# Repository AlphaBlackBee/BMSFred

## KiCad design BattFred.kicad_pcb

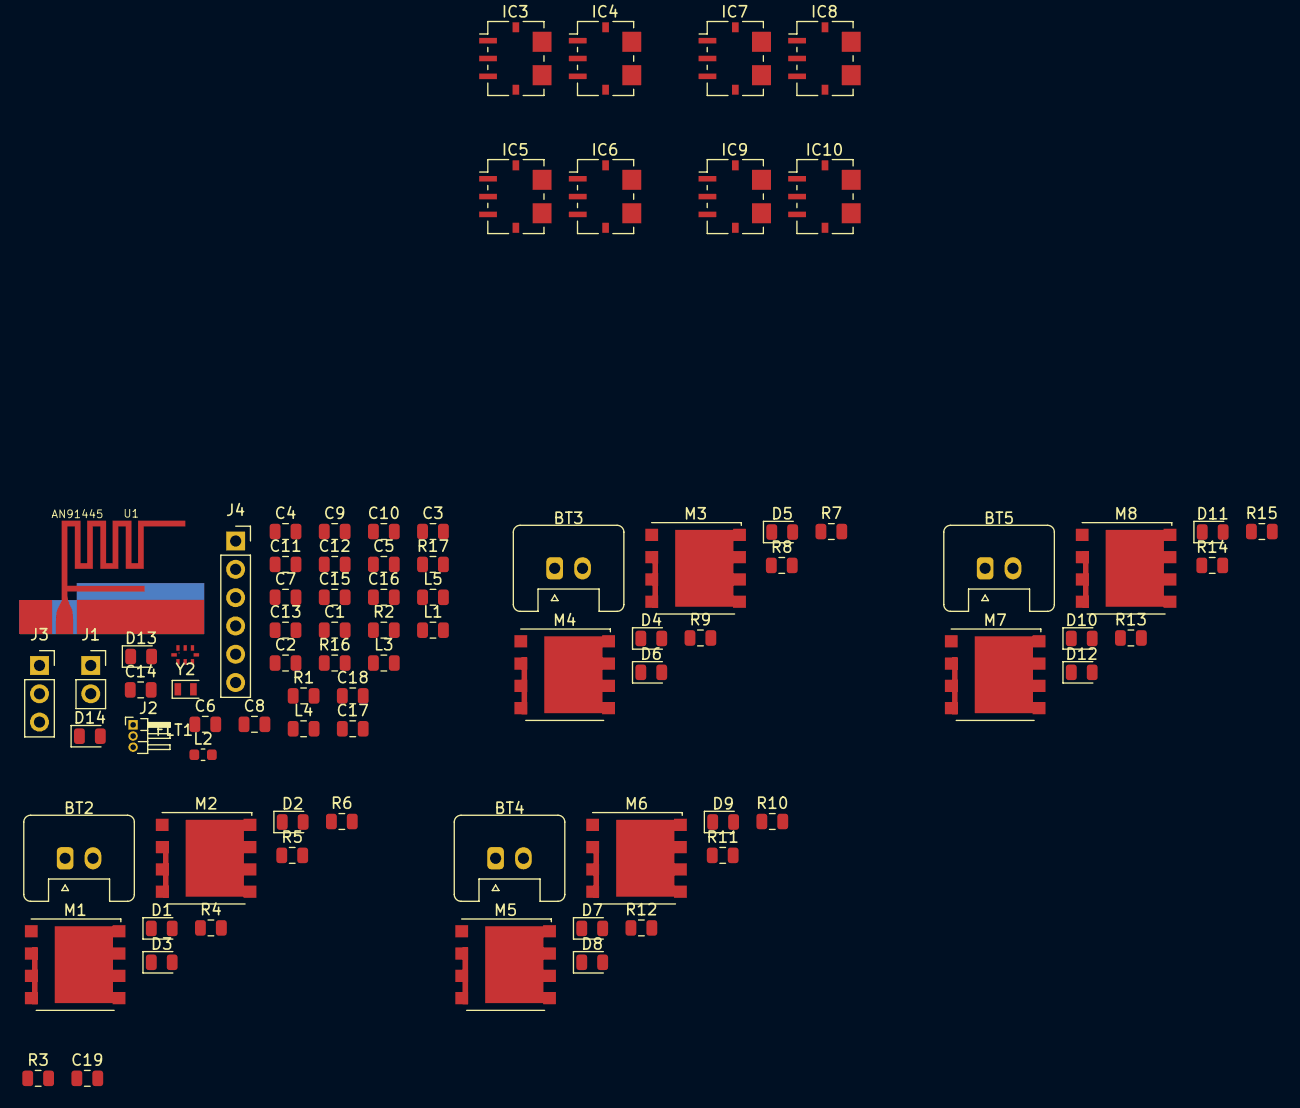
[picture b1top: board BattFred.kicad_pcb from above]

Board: 2 copper layers, 82 parts (0 on the bottom side), 52 nets, no tracks yet.

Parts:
BT2, BT3, BT4, BT5: Battery_Cell; Stocko_MKS_1651-6-0-202_1x2_P2.50mm_Vertical
C1: 0.8pF; C_0805_2012Metric
C2: 0.3pF; C_0805_2012Metric
C3, C4: 10p; C_0805_2012Metric
C5, C14: 10nF; C_0805_2012Metric
C6: ND; C_0805_2012Metric
C7: 1.2pF; C_0805_2012Metric
C8, C11, C12, C13, C15: 100nF; C_0805_2012Metric
C9, C10, C17: 4.7uF; C_0805_2012Metric
C16: 100pF; C_0805_2012Metric
C18: 1uF; C_0805_2012Metric
C19: 47nF; C_0805_2012Metric
D1, D3, D4, D6, D7, D9, D10, D12: RED; LED_0805_2012Metric
D2, D5, D8, D11: GREEN; LED_0805_2012Metric
D13, D14: LED; LED_0805_2012Metric
FLT1: LFL212G45TC1A007
IC3, IC4, IC5, IC6, IC7, IC8, IC9, IC10: ACS780LLRTR-050U-T; Allegro_PSOF-7_4.8x6.4mm_P1.60mm
J1: Conn_01x02_Male; PinSocket_1x02_P2.54mm_Vertical
J2: Conn_01x03_Male; PinHeader_1x03_P1.00mm_Horizontal
J3: Conn_01x03_Male; PinSocket_1x03_P2.54mm_Vertical
J4: Conn_01x06; PinSocket_1x06_P2.54mm_Vertical
L1: 1.4 2.7nH; L_0805_2012Metric
L2: LQG15HS3N6S02B; L_0603_1608Metric
L3, L4: 10nH; L_0805_2012Metric
L5: BLM31KN601SN1L; L_0805_2012Metric
M1, M2, M3, M4, M5, M6, M7, M8: MNMOS; PQFN_8x8
R1: 1k; R_0805_2012Metric
R2: 10k; R_0805_2012Metric
R3: 39k; R_0805_2012Metric
R4, R5, R6, R7, R8, R9, R10, R11, R12, R13, R14, R15, R16, R17: R; R_0805_2012Metric
U1: AN91445
Y2: 32.768KHz; Crystal_SMD_2012-2Pin_2.0x1.2mm

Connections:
GND: C1.2, C2.2, C3.2, C4.2, C6.2, C7.2, C8.1, C9.2, C10.1, C11.1, C12.1, C13.1, C14.2, C15.1, C16.1, C17.1, C18.1, C19.2, D2.1, D5.1, D8.1, D11.1, D13.1, D14.1, FLT1.1, IC3.2, IC4.2, IC5.2, IC6.2, IC7.2, IC8.2, IC9.2, IC10.2, J4.1, R2.1, R3.2, U1.2
GNDPWR: M2.3, M4.3, M6.3, M8.3
unnamed: BT2.1, IC3.6
unnamed: BT2.2, IC4.5
unnamed: BT3.1, IC5.6
unnamed: BT3.2, IC6.5
unnamed: BT4.1, IC7.6
unnamed: BT4.2, IC8.5
unnamed: BT5.1, IC9.6
unnamed: BT5.2, IC10.5
unnamed: C2.1, FLT1.8, L1.2
unnamed: C5.1, FLT1.4
unnamed: C5.2, C6.1, L2.2
unnamed: C7.1, L2.1, U1.1
unnamed: D1.1, M1.2
unnamed: D1.2, R4.1
unnamed: D2.2, R5.1
unnamed: D3.1, M2.2
unnamed: D3.2, R6.2
unnamed: D4.1, M3.2
unnamed: D4.2, R7.1
unnamed: D5.2, R8.1
unnamed: D6.1, M4.2
unnamed: D6.2, R9.2
unnamed: D7.1, M5.2
unnamed: D7.2, R10.1
unnamed: D8.2, R11.1
unnamed: D9.1, M6.2
unnamed: D9.2, R12.2
unnamed: D10.1, M7.2
unnamed: D10.2, R13.1
unnamed: D11.2, R14.1
unnamed: D12.1, M8.2
unnamed: D12.2, R15.2
unnamed: D13.2, R16.1
unnamed: D14.2, R17.1
unnamed: IC3.5, M1.3
unnamed: IC4.6, M2.1
unnamed: IC5.5, M3.3
unnamed: IC6.6, M4.1
unnamed: IC7.5, M5.3
unnamed: IC8.6, M6.1
unnamed: IC9.5, M7.3
unnamed: IC10.6, M8.1
unnamed: J2.1, R2.2
OSC32K_IN: C3.1, Y2.1
OSC32K_OUT: C4.1, Y2.2
RF1: C1.1, L1.1
VCC: C8.2, C9.1, C11.2, C12.2, C13.2, C15.2, C16.2, C17.2, C19.1, IC3.1, IC4.1, IC5.1, IC6.1, IC7.1, IC8.1, IC9.1, IC10.1, J2.3, J3.1, J4.6, L3.1, L4.2, L5.2, M7.1
VCCA: C14.1, C18.2, L5.1
VCharge: M1.1, M3.1, M5.1
VFBSOUT: C10.2, L3.2
